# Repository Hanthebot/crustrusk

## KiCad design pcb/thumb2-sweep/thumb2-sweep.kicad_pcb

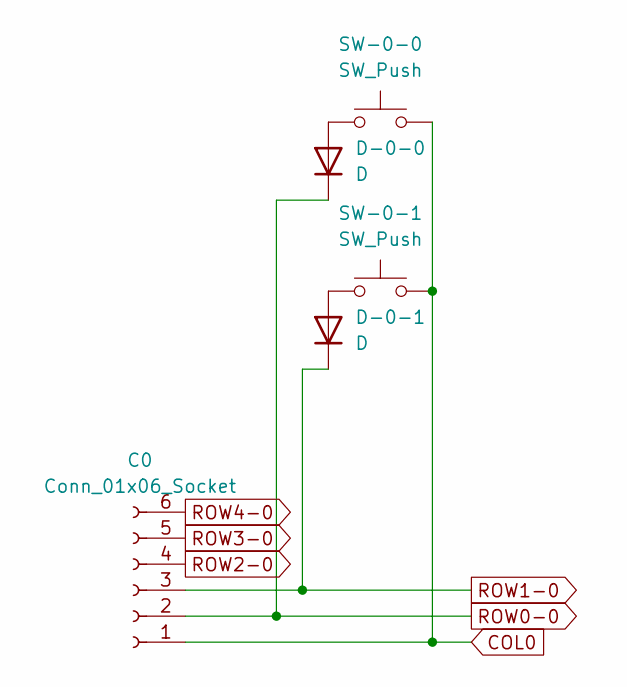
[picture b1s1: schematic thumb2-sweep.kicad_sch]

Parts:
C0: Conn_01x06_Socket; reversible JST_PH_S6B-PH-K_1x06_P2.00mm_Horizontal
D-0-0, D-0-1: D; Diode_TH_SMD_REVERSIBLE
SW-0-0, SW-0-1: SW_Push; Kailh_hotswap_only_socket_MX_optional_reversible-MIRROR

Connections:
COL0: C0.1, SW-0-0.2, SW-0-1.2
unnamed: D-0-0.2 (A), SW-0-0.1
unnamed: D-0-1.2 (A), SW-0-1.1
ROW0-0: C0.2, D-0-0.1 (K)
ROW1-0: C0.3, D-0-1.1 (K)
ROW2-0: C0.4
ROW3-0: C0.5
ROW4-0: C0.6

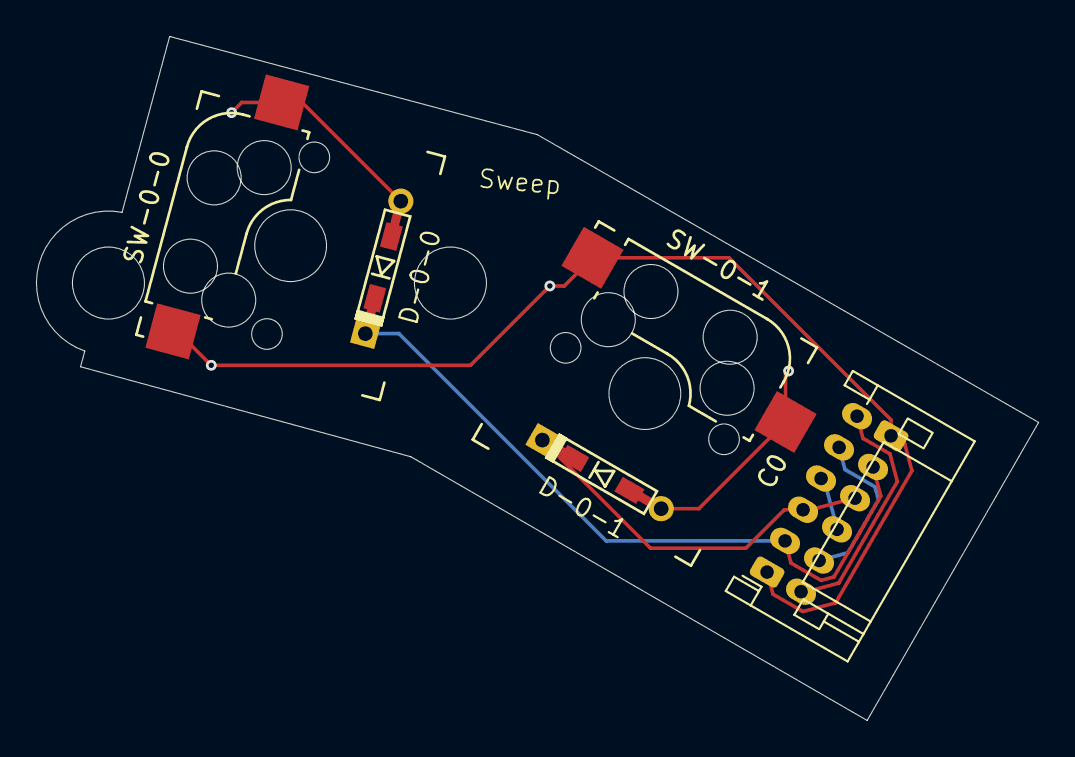
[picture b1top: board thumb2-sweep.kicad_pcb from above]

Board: 2 copper layers, 55.7 x 38.0 mm, 5 parts (0 on the bottom side), 5 nets.
